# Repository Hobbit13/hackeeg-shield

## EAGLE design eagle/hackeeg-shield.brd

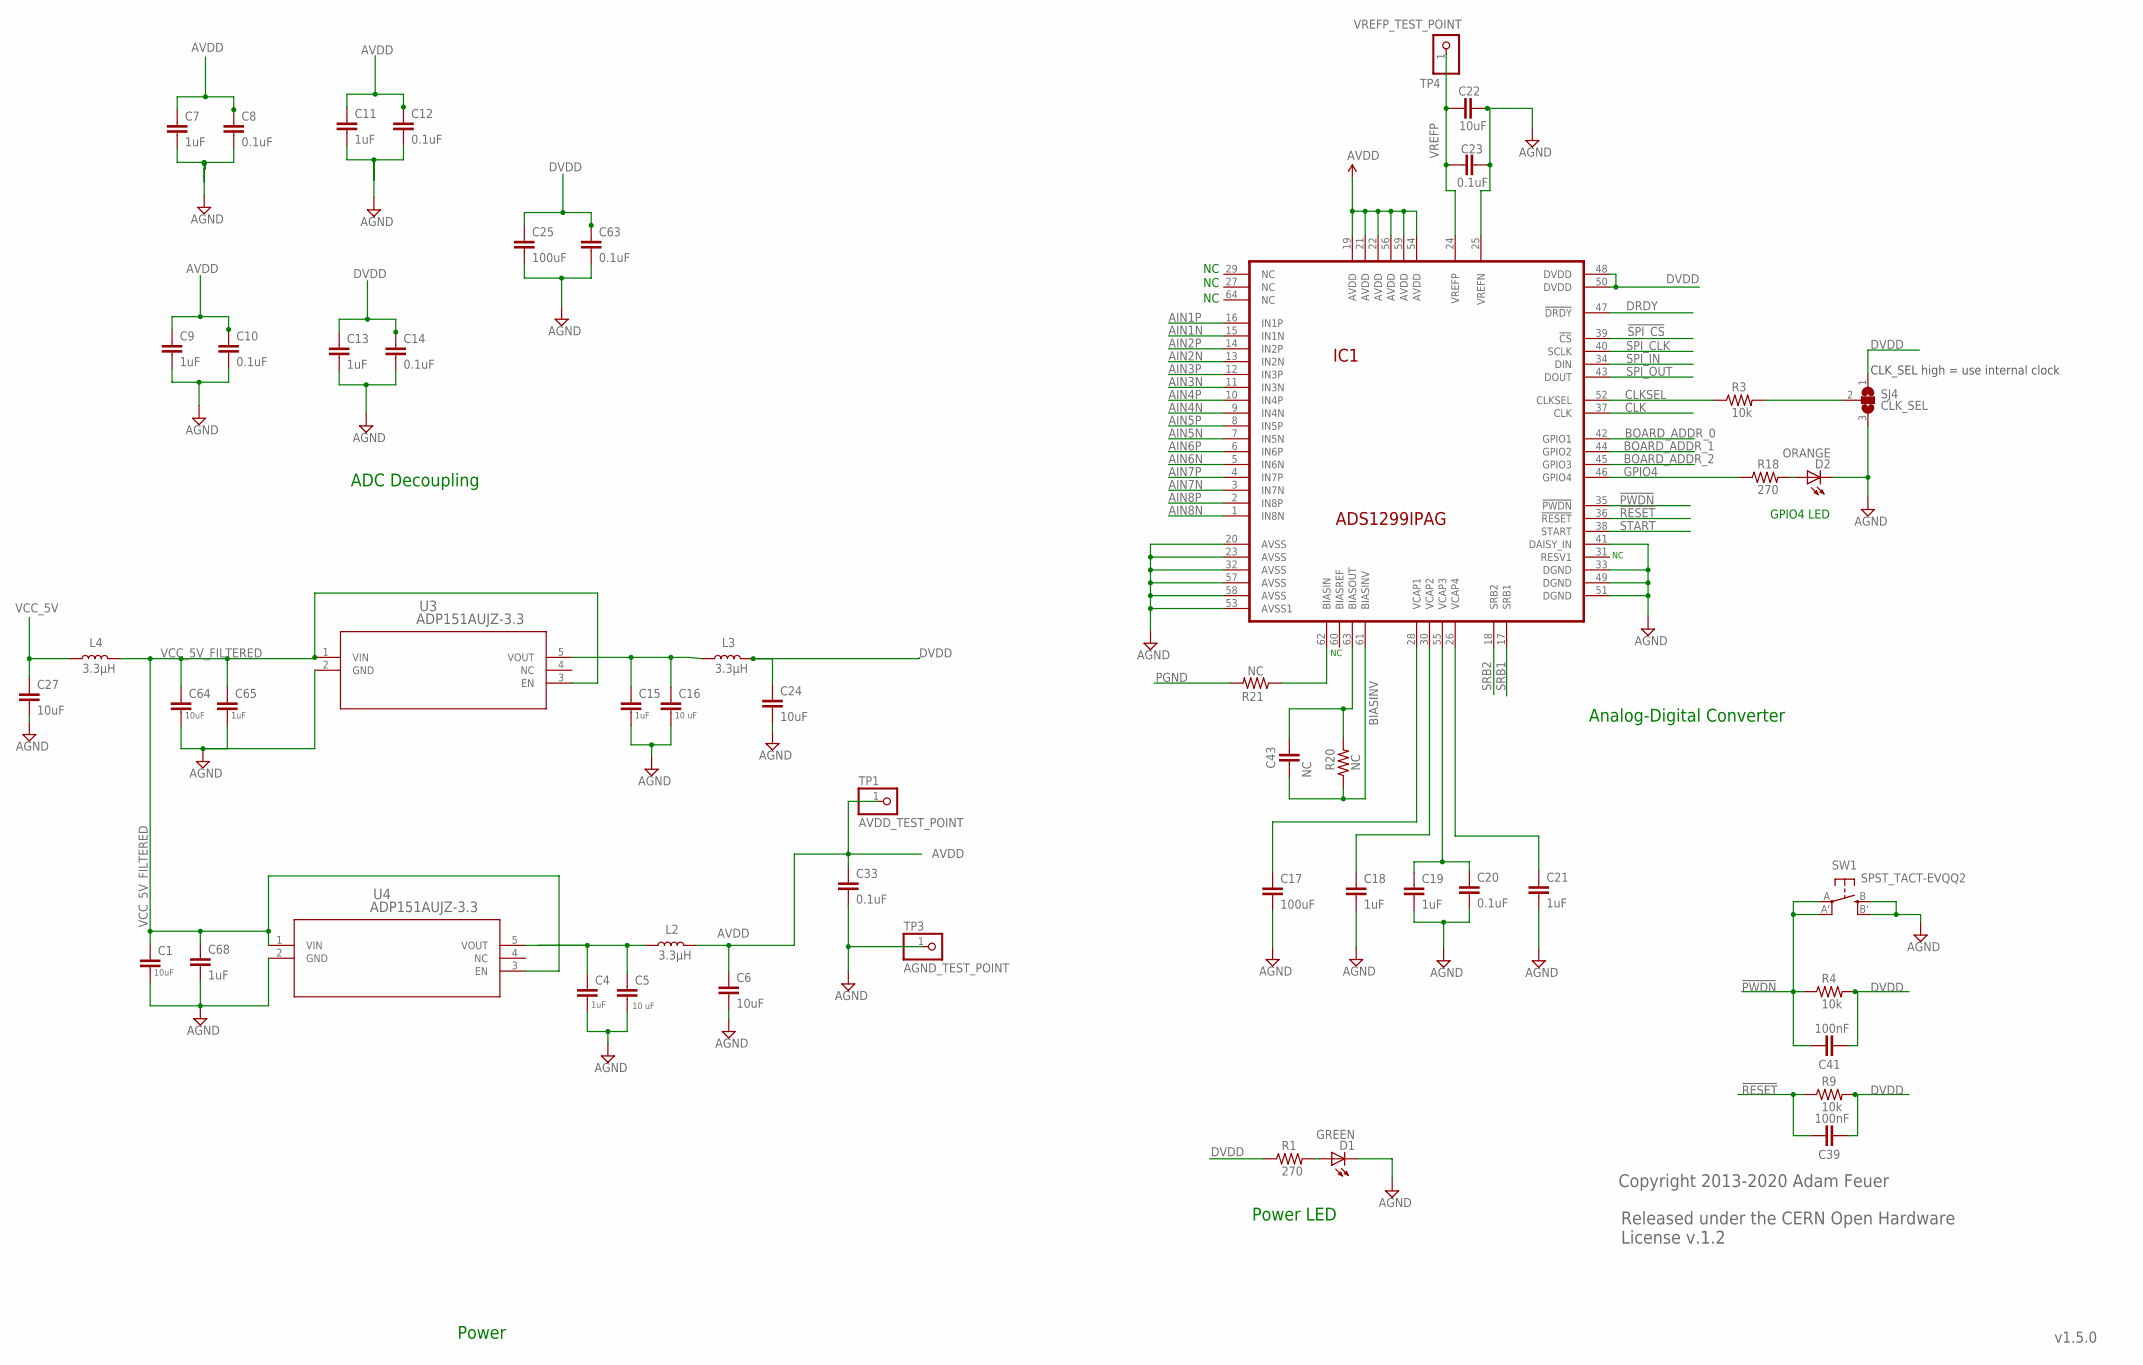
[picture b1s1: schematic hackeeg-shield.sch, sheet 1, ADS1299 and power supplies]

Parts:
C1, C6, C22, C24, C27, C64: 10uF; 0603-CAP
C4, C7, C9, C11, C13, C15, C18, C19, C21, C65, C68: 1uF; 0603-CAP
C5, C16: 10 uF; 0603-CAP
C8, C10, C12, C14, C20, C23, C33, C63: 0.1uF; 0603-CAP
C17, C25: 100uF; 1210
C39, C41: 100nF; 0603-CAP
C43: NC; 0603-CAP
D1: GREEN; LED-1206
D2: ORANGE; LED-1206
IC1: ADS1299IPAG; TQFP64
L2, L3, L4: 3.3μH; 0805-WIDE
R1, R18: 270; 0603-RES
R3, R4, R9: 10k; 0603-RES
R20, R21: NC; 0603-RES
SJ4: CLK_SEL; SJ_2
SW1: SPST_TACT-EVQQ2; EVQ-Q2
TP1: AVDD_TEST_POINT; 1X01
TP3: AGND_TEST_POINT; 1X01
TP4: VREFP_TEST_POINT; 1X01
U3, U4: ADP151AUJZ-3.3; UJ_5_ADI

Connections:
!PWDN: C41.1, IC1.35 (!PWDN), R4.1, SW1.A, SW1.A' (P1)
!RESET: C39.1, IC1.36 (!RESET), R9.1
!SPI_CS: IC1.39 (!CS); also elsewhere on the board
AGND: C1.2, C4.2, C5.2, C6.2, C7.2, C8.2, C9.2, C10.2, C11.2, C12.2, C13.2, C14.2, C15.2, C16.2, C17.2, C18.2, C19.2, C20.2, C21.2, C22.2, C23.2, C24.2, C25.2, C27.2, C33.2, C63.2, C64.2, C65.2, C68.2, D1.C, D2.C, IC1.20 (AVSS), IC1.23 (AVSS), IC1.25 (VREFN), IC1.32 (AVSS), IC1.33 (DGND), IC1.41 (DAISY_IN), IC1.49 (DGND), IC1.51 (DGND), IC1.53 (AVSS1), IC1.57 (AVSS), IC1.58 (AVSS), SJ4.3, SW1.B (S), SW1.B' (S1), TP3.1, U3.2 (GND), U4.2 (GND); also elsewhere on the board
AIN1N: IC1.15 (IN1N); also elsewhere on the board
AIN1P: IC1.16 (IN1P); also elsewhere on the board
AIN2N: IC1.13 (IN2N); also elsewhere on the board
AIN2P: IC1.14 (IN2P); also elsewhere on the board
AIN3N: IC1.11 (IN3N); also elsewhere on the board
AIN3P: IC1.12 (IN3P); also elsewhere on the board
AIN4N: IC1.9 (IN4N); also elsewhere on the board
AIN4P: IC1.10 (IN4P); also elsewhere on the board
AIN5N: IC1.7 (IN5N); also elsewhere on the board
AIN5P: IC1.8 (IN5P); also elsewhere on the board
AIN6N: IC1.5 (IN6N); also elsewhere on the board
AIN6P: IC1.6 (IN6P); also elsewhere on the board
AIN7N: IC1.3 (IN7N); also elsewhere on the board
AIN7P: IC1.4 (IN7P); also elsewhere on the board
AIN8N: IC1.1 (IN8N); also elsewhere on the board
AIN8P: IC1.2 (IN8P); also elsewhere on the board
AVDD: C6.1, C7.1, C8.1, C9.1, C10.1, C11.1, C12.1, C33.1, IC1.19 (AVDD), IC1.21 (AVDD), IC1.22 (AVDD), IC1.54 (AVDD), IC1.56 (AVDD), IC1.59 (AVDD), L2.2, TP1.1; also elsewhere on the board
BIASINV: C43.2, IC1.61 (BIASINV), R20.1; also elsewhere on the board
BOARD_ADDR_0: IC1.42 (GPIO1)
BOARD_ADDR_1: IC1.44 (GPIO2)
BOARD_ADDR_2: IC1.45 (GPIO3)
CLK: IC1.37 (CLK); also elsewhere on the board
CLKSEL: IC1.52 (CLKSEL), R3.1
DRDY: IC1.47 (!DRDY); also elsewhere on the board
DVDD: C13.1, C14.1, C24.1, C25.1, C39.2, C41.2, C63.1, IC1.48 (DVDD), IC1.50 (DVDD), L3.2, R1.1, R4.2, R9.2, SJ4.1; also elsewhere on the board
GPIO4: IC1.46 (GPIO4), R18.1
unnamed: C4.1, C5.1, L2.1, U4.5 (VOUT)
unnamed: C15.1, C16.1, L3.1, U3.5 (VOUT)
unnamed: C17.1, IC1.28 (VCAP1)
unnamed: C18.1, IC1.30 (VCAP2)
unnamed: C19.1, C20.1, IC1.55 (VCAP3)
unnamed: C21.1, IC1.26 (VCAP4)
unnamed: D2.A, R18.2
unnamed: D1.A, R1.2
unnamed: R3.2, SJ4.2
unnamed: C43.1, IC1.63 (BIASOUT), R20.2
unnamed: IC1.62 (BIASIN), R21.1
PGND: R21.2; also elsewhere on the board
SPI_CLK: IC1.40 (SCLK); also elsewhere on the board
SPI_IN: IC1.34 (DIN); also elsewhere on the board
SPI_OUT: IC1.43 (DOUT); also elsewhere on the board
SRB1: IC1.17 (SRB1); also elsewhere on the board
SRB2: IC1.18 (SRB2); also elsewhere on the board
START: IC1.38 (START); also elsewhere on the board
VCC_5V: C27.1, L4.1; also elsewhere on the board
VCC_5V_FILTERED: C1.1, C64.1, C65.1, C68.1, L4.2, U3.1 (VIN), U3.3 (EN), U4.1 (VIN), U4.3 (EN)
VREFP: C22.1, C23.1, IC1.24 (VREFP), TP4.1

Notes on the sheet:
Released under the CERN Open Hardware License v.1.2
Copyright 2013-2020 Adam Feuer
v1.5.0
ADC Decoupling
Power
Analog-Digital Converter
GPIO4 LED
Power LED
CLK_SEL high = use internal clock

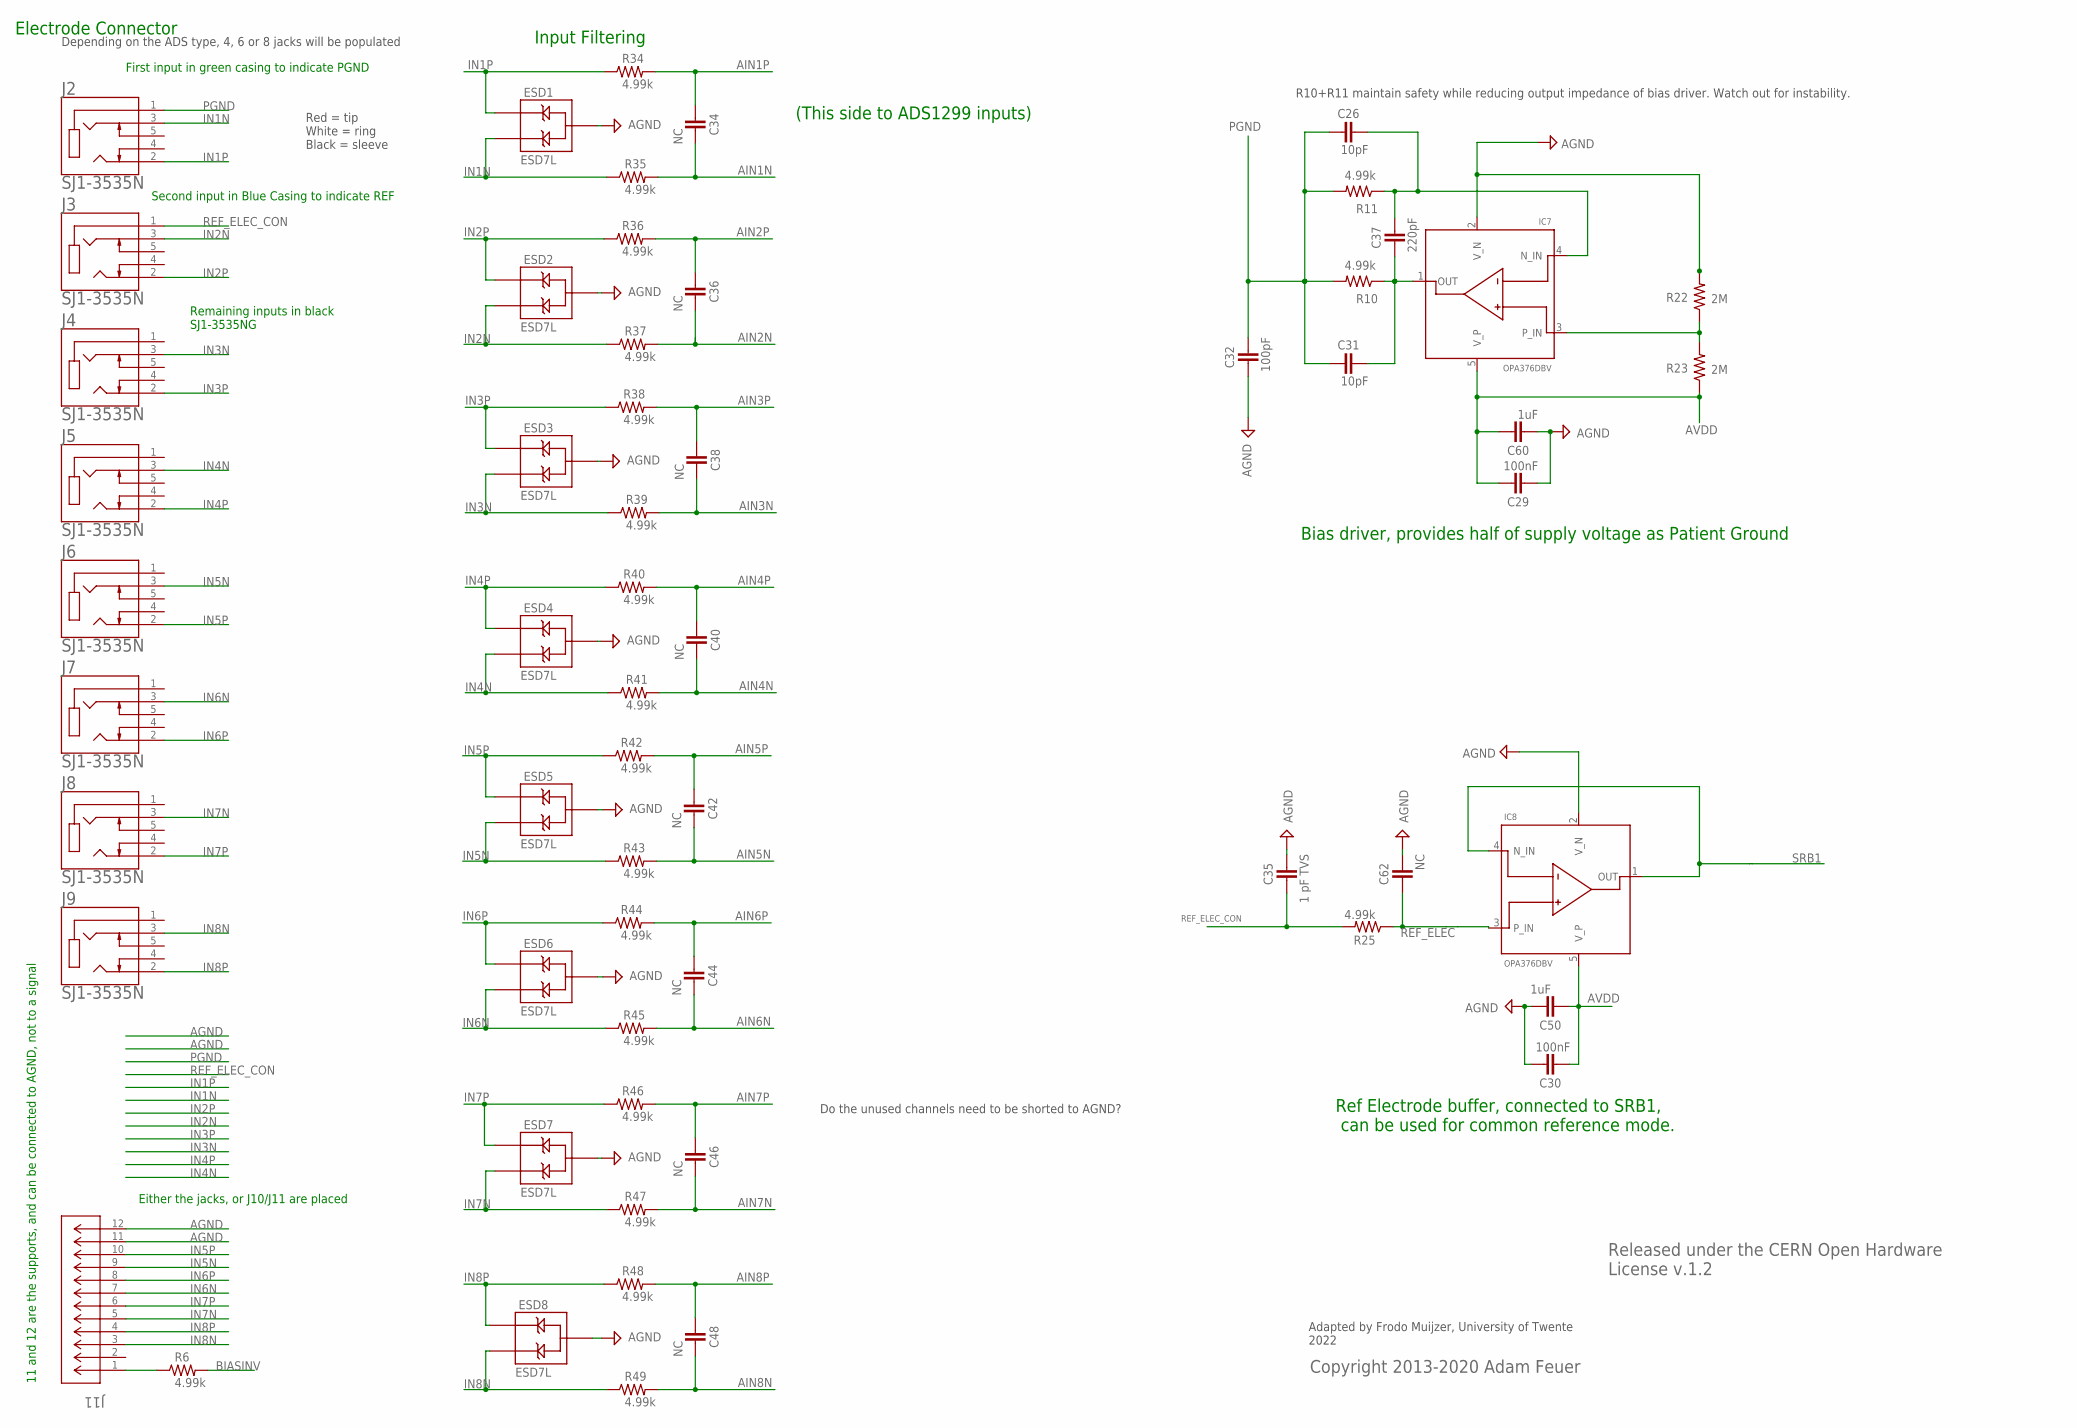
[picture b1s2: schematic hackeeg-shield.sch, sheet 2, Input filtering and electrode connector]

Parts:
C26, C31: 10pF; 0603-CAP
C29, C30: 100nF; 0603-CAP
C32: 100pF; 0603-CAP
C34, C36, C38, C40, C42, C44, C46, C48, C62: NC; 0603-CAP
C35: 1 pF TVS; 0603-CAP
C37: 220pF; 0603-CAP
C50, C60: 1uF; 0603-CAP
ESD1, ESD2, ESD3, ESD4, ESD5, ESD6, ESD7, ESD8: ESD7L; SOT-723
IC7, IC8: OPA376DBV; SOT23-5
J2, J3, J4, J5, J6, J7, J8, J9: SJ1-3535N; CUI_SJ1-3535N
J11: 533981071; CON_533981071
R6, R10, R11, R25, R34, R35, R36, R37, R38, R39, R40, R41, R42, R43, R44, R45, R46, R47, R48, R49: 4.99k; 0603-RES
R22, R23: 2M; 0603-RES

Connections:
AGND: C29.2, C30.1, C32.1, C35.2, C50.2, C60.2, C62.2, ESD1.P$3, ESD2.P$3, ESD3.P$3, ESD4.P$3, ESD5.P$3, ESD6.P$3, ESD7.P$3, ESD8.P$3, IC7.2 (V_N), IC8.2 (V_N), J11.11, J11.12, R22.2; also elsewhere on the board
AIN1N: C34.2, R35.2; also elsewhere on the board
AIN1P: C34.1, R34.2; also elsewhere on the board
AIN2N: C36.2, R37.2; also elsewhere on the board
AIN2P: C36.1, R36.2; also elsewhere on the board
AIN3N: C38.2, R39.2; also elsewhere on the board
AIN3P: C38.1, R38.2; also elsewhere on the board
AIN4N: C40.2, R41.2; also elsewhere on the board
AIN4P: C40.1, R40.2; also elsewhere on the board
AIN5N: C42.2, R43.2; also elsewhere on the board
AIN5P: C42.1, R42.2; also elsewhere on the board
AIN6N: C44.2, R45.2; also elsewhere on the board
AIN6P: C44.1, R44.2; also elsewhere on the board
AIN7N: C46.2, R47.2; also elsewhere on the board
AIN7P: C46.1, R46.2; also elsewhere on the board
AIN8N: C48.2, R49.2; also elsewhere on the board
AIN8P: C48.1, R48.2; also elsewhere on the board
AVDD: C29.1, C30.2, C50.1, C60.1, IC7.5 (V_P), IC8.5 (V_P), R23.1; also elsewhere on the board
BIASINV: R6.2; also elsewhere on the board
IN1N: ESD1.P$2, J2.3, R35.1
IN1P: ESD1.P$1, J2.2, R34.1
IN2N: ESD2.P$2, J3.3, R37.1
IN2P: ESD2.P$1, J3.2, R36.1
IN3N: ESD3.P$2, J4.3, R39.1
IN3P: ESD3.P$1, J4.2, R38.1
IN4N: ESD4.P$2, J5.3, R41.1
IN4P: ESD4.P$1, J5.2, R40.1
IN5N: ESD5.P$2, J6.3, J11.9, R43.1
IN5P: ESD5.P$1, J6.2, J11.10, R42.1
IN6N: ESD6.P$2, J7.3, J11.7, R45.1
IN6P: ESD6.P$1, J7.2, J11.8, R44.1
IN7N: ESD7.P$2, J8.3, J11.5, R47.1
IN7P: ESD7.P$1, J8.2, J11.6, R46.1
IN8N: ESD8.P$2, J9.3, J11.3, R49.1
IN8P: ESD8.P$1, J9.2, J11.4, R48.1
unnamed: J11.1, R6.1
unnamed: IC7.3 (P_IN), R22.1, R23.2
unnamed: C31.2, C37.1, IC7.1 (OUT), R10.1
unnamed: C26.2, C37.2, IC7.4 (N_IN), R11.1
PGND: C26.1, C31.1, C32.2, J2.1, R10.2, R11.2; also elsewhere on the board
REF_ELEC: C62.1, IC8.3 (P_IN), R25.1
REF_ELEC_CON: C35.1, J3.1, R25.2
SRB1: IC8.1 (OUT), IC8.4 (N_IN); also elsewhere on the board

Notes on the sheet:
Electrode Connector
Ref Electrode buffer, connected to SRB1, can be used for common reference mode.
Released under the CERN Open Hardware License v.1.2
Copyright 2013-2020 Adam Feuer
Input Filtering
(This side to ADS1299 inputs)
Red = tip White = ring Black = sleeve
R10+R11 maintain safety while reducing output impedance of bias driver. Watch out for instability.
Depending on the ADS type, 4, 6 or 8 jacks will be populated
Do the unused channels need to be shorted to AGND?
Adapted by Frodo Muijzer, University of Twente 2022
Bias driver, provides half of supply voltage as Patient Ground
First input in green casing to indicate PGND
Second input in Blue Casing to indicate REF
Remaining inputs in black SJ1-3535NG
11 and 12 are the supports, and can be connected to AGND, not to a signal
Either the jacks, or J10/J11 are placed

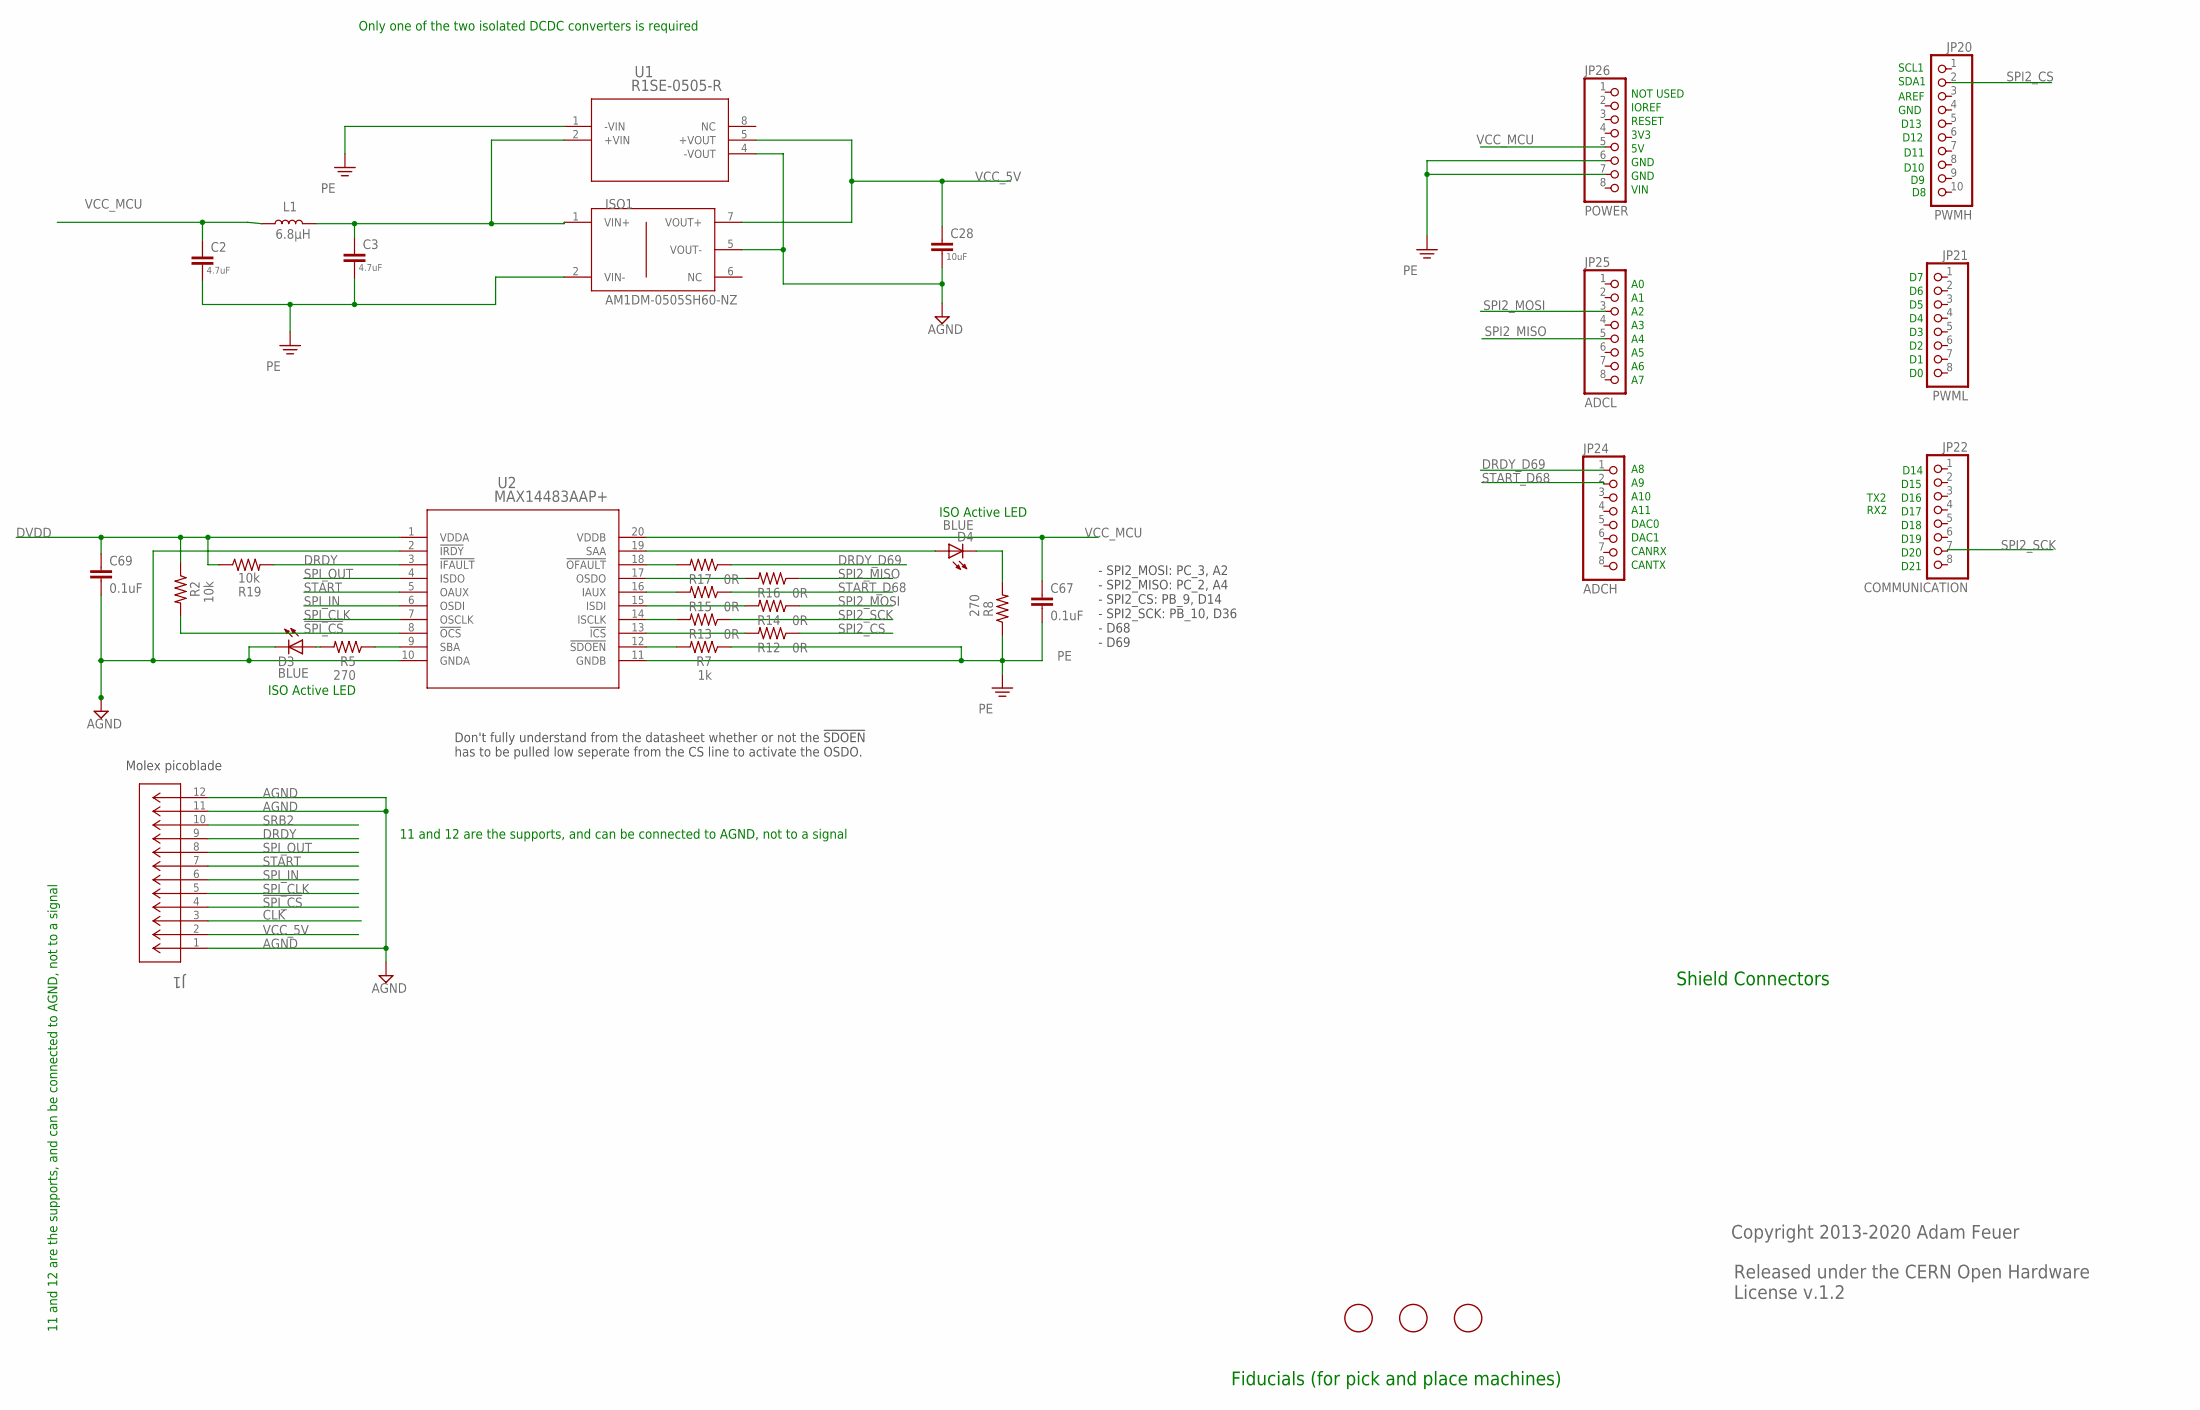
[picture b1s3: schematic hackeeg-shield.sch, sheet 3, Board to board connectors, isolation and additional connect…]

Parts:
C2, C3: 4.7uF; 0603-CAP
C28: 10uF; 0603-CAP
C67, C69: 0.1uF; 0603-CAP
D3, D4: BLUE; LED-1206
ISO1: AM1DM-0505SH60-NZ; SIP1005W50P254L1965H1265Q7
J1: 533981071; CON_533981071
JP20: PWMH; 1X10
JP21: PWML; 1X08
JP22: COMMUNICATION; 1X08
JP24: ADCH; 1X08
JP25: ADCL; 1X08
JP26: POWER; 1X08
L1: 6.8μH; 0805-WIDE
R2, R19: 10k; 0603-RES
R5, R8: 270; 0603-RES
R7: 1k; 0603-RES
R12, R13, R14, R15, R16, R17: 0R; 0603-RES
U1: R1SE-0505-R; R1SE-0505-R_RCP
U2: MAX14483AAP+; 21-0056C_20_MXM
U$2, U$5, U$6: FIDUCIAL; FIDUCIAL_1MM

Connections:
!SPI_CS: J1.4, R2.2, U2.8 (!OCS); also elsewhere on the board
AGND: C28.2, C69.2, D3.C, ISO1.5 (VOUT-), J1.1, J1.11, J1.12, U1.4 (-VOUT), U2.2 (!IRDY), U2.10 (GNDA); also elsewhere on the board
CLK: J1.3; also elsewhere on the board
DRDY: J1.9, R19.2, U2.3 (!IFAULT); also elsewhere on the board
DRDY_D69: JP24.1, R17.1
DVDD: C69.1, R2.1, R19.1, U2.1 (VDDA); also elsewhere on the board
unnamed: C3.1, ISO1.1 (VIN+), L1.2, U1.2 (+VIN)
unnamed: D4.A, U2.19 (SAA)
unnamed: D3.A, R5.2
unnamed: R5.1, U2.9 (SBA)
unnamed: R17.2, U2.18 (!OFAULT)
unnamed: D4.C, R8.2
unnamed: R12.2, U2.13 (!ICS)
unnamed: R13.2, U2.14 (ISCLK)
unnamed: R14.2, U2.15 (ISDI)
unnamed: R15.2, U2.16 (IAUX)
unnamed: R16.2, U2.17 (OSDO)
unnamed: R7.2, U2.12 (!SDOEN)
PE: C2.2, C3.2, C67.2, ISO1.2 (VIN-), JP26.6, JP26.7, R7.1, R8.1, U1.1 (-VIN), U2.11 (GNDB)
SPI2_CS: JP20.2, R12.1
SPI2_MISO: JP25.5, R16.1
SPI2_MOSI: JP25.3, R14.1
SPI2_SCK: JP22.7, R13.1
SPI_CLK: J1.5, U2.7 (OSCLK); also elsewhere on the board
SPI_IN: J1.6, U2.6 (OSDI); also elsewhere on the board
SPI_OUT: J1.8, U2.4 (ISDO); also elsewhere on the board
SRB2: J1.10; also elsewhere on the board
START: J1.7, U2.5 (OAUX); also elsewhere on the board
START_D68: JP24.2, R15.1
VCC_5V: C28.1, ISO1.7 (VOUT+), J1.2, U1.5 (+VOUT); also elsewhere on the board
VCC_MCU: C2.1, C67.1, JP26.5, L1.1, U2.20 (VDDB)

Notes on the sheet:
Released under the CERN Open Hardware License v.1.2
Copyright 2013-2020 Adam Feuer
Shield Connectors
SCL1
SDA1
AREF
GND
D14
D15
D16
D17
D18
D19
D20
D21
A10
A11
DAC0
DAC1
CANRX
CANTX
NOT USED
IOREF
RESET
3V3
VIN
Fiducials (for pick and place machines)
TX2
RX2
D13
D12
D11
D10
Only one of the two isolated DCDC converters is required
ISO Active LED
- SPI2_MOSI: PC_3, A2 - SPI2_MISO: PC_2, A4 - SPI2_CS: PB_9, D14 - SPI2_SCK: PB_10, D36 - D68 - D69
Don't fully understand from the datasheet whether or not the !SDOEN has to be pulled low seperate from the CS line to activate the OSDO.
Molex picoblade
11 and 12 are the supports, and can be connected to AGND, not to a signal

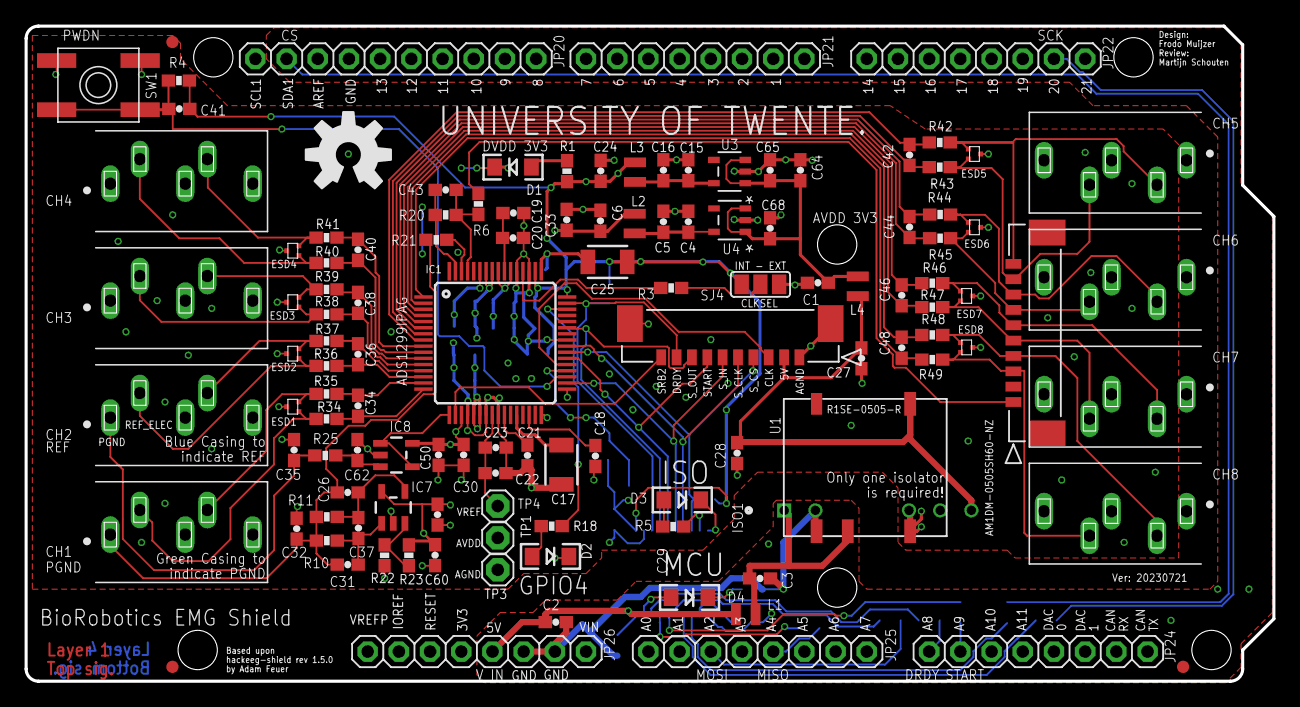
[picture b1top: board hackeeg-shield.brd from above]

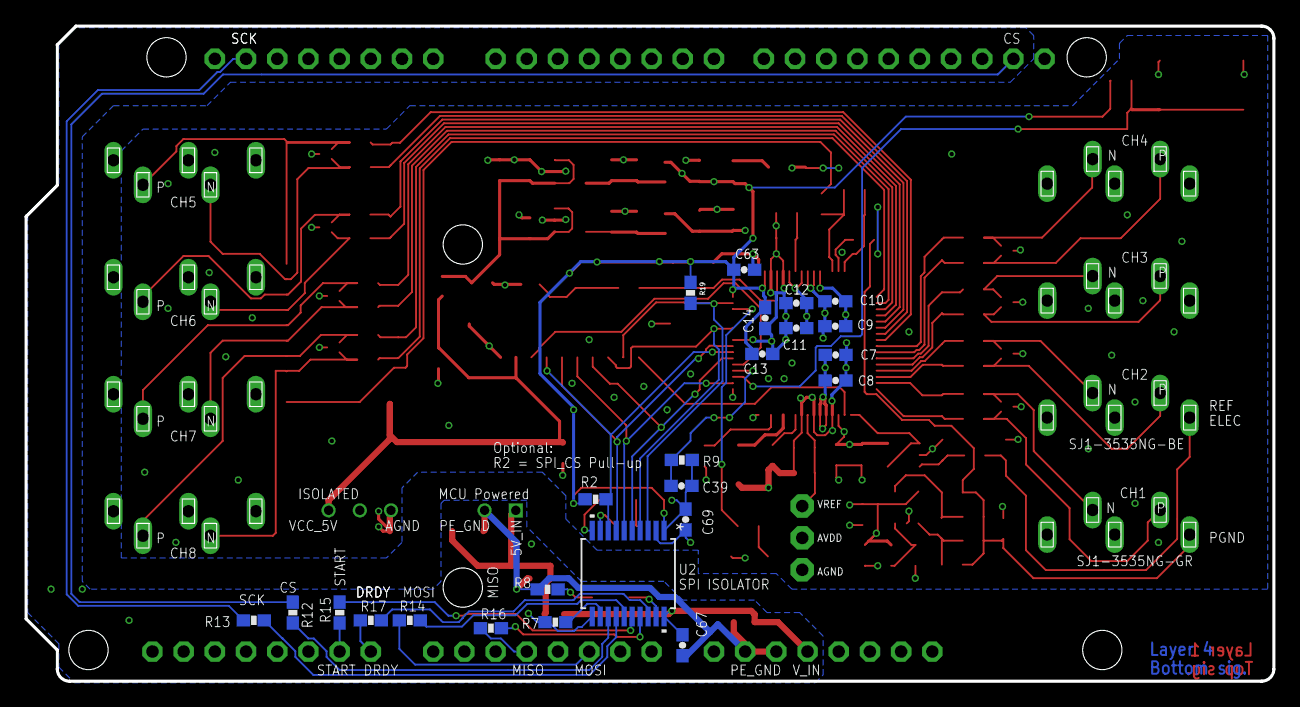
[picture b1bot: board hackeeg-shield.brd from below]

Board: 4 copper layers, 101.6 x 53.3 mm, 144 parts (24 on the bottom side), 90 nets.

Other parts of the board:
U$1: OSHW-LOGO-L

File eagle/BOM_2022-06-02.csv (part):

"Part";"Value";"Device";"Package";"Description";"AVAILABILITY";"COPYRIGHT";"CUI_PURCHASE_URL";"DESCRIPTION";"MANUFACTURER_PART_NUMBER";"MF";"MFR_NAME";"MP";"PACKAGE";"POPULARITY";"PRICE";"PROD_ID";"PURCHASE-URL";"VALUE";
"C1";"10uF";"CAP0603-CAP";"0603-CAP";"Capacitor";"";"";"";"";"";"";"";"";"";"";"";"";"";"";
"C2";"4.7uF";"CAP0603-CAP";"0603-CAP";"Capacitor";"";"";"";"";"";"";"";"";"";"";"";"";"";"";
"C3";"4.7uF";"CAP0603-CAP";"0603-CAP";"Capacitor";"";"";"";"";"";"";"";"";"";"";"";"";"";"";
"C4";"1uF";"CAP0603-CAP";"0603-CAP";"Capacitor";"";"";"";"";"";"";"";"";"";"";"";"";"";"";
"C5";"10 uF";"CAP0603-CAP";"0603-CAP";"Capacitor";"";"";"";"";"";"";"";"";"";"";"";"";"";"";
"C6";"10uF";"CAP0603-CAP";"0603-CAP";"Capacitor";"";"";"";"";"";"";"";"";"";"";"";"";"";"";
"C7";"1uF";"CAP0603-CAP";"0603-CAP";"Capacitor";"";"";"";"";"";"";"";"";"";"";"";"";"";"";
"C8";"0.1uF";"CAP0603-CAP";"0603-CAP";"Capacitor";"";"";"";"";"";"";"";"";"";"";"";"";"";"";
"C9";"1uF";"CAP0603-CAP";"0603-CAP";"Capacitor";"";"";"";"";"";"";"";"";"";"";"";"";"";"";
"C10";"0.1uF";"CAP0603-CAP";"0603-CAP";"Capacitor";"";"";"";"";"";"";"";"";"";"";"";"";"";"";
"C11";"1uF";"CAP0603-CAP";"0603-CAP";"Capacitor";"";"";"";"";"";"";"";"";"";"";"";"";"";"";
"C12";"0.1uF";"CAP0603-CAP";"0603-CAP";"Capacitor";"";"";"";"";"";"";"";"";"";"";"";"";"";"";
"C13";"1uF";"CAP0603-CAP";"0603-CAP";"Capacitor";"";"";"";"";"";"";"";"";"";"";"";"";"";"";
"C14";"0.1uF";"CAP0603-CAP";"0603-CAP";"Capacitor";"";"";"";"";"";"";"";"";"";"";"";"";"";"";
"C15";"1uF";"CAP0603-CAP";"0603-CAP";"Capacitor";"";"";"";"";"";"";"";"";"";"";"";"";"";"";
"C16";"10 uF";"CAP0603-CAP";"0603-CAP";"Capacitor";"";"";"";"";"";"";"";"";"";"";"";"";"";"";
"C17";"100uF";"CAP1210";"1210";"Capacitor";"";"";"";"";"";"";"";"";"";"";"";"";"";"";
"C18";"1uF";"CAP0603-CAP";"0603-CAP";"Capacitor";"";"";"";"";"";"";"";"";"";"";"";"";"";"";
"C19";"1uF";"CAP0603-CAP";"0603-CAP";"Capacitor";"";"";"";"";"";"";"";"";"";"";"";"";"";"";
"C20";"0.1uF";"CAP0603-CAP";"0603-CAP";"Capacitor";"";"";"";"";"";"";"";"";"";"";"";"";"";"";
"C21";"1uF";"CAP0603-CAP";"0603-CAP";"Capacitor";"";"";"";"";"";"";"";"";"";"";"";"";"";"";
"C22";"10uF";"CAP0603-CAP";"0603-CAP";"Capacitor";"";"";"";"";"";"";"";"";"";"";"";"";"";"";
"C23";"0.1uF";"CAP0603-CAP";"0603-CAP";"Capacitor";"";"";"";"";"";"";"";"";"";"";"";"";"";"";
"C24";"10uF";"CAP0603-CAP";"0603-CAP";"Capacitor";"";"";"";"";"";"";"";"";"";"";"";"";"";"";
"C25";"100uF";"CAP1210";"1210";"Capacitor";"";"";"";"";"";"";"";"";"";"";"";"";"";"";
"C26";"10pF";"CAP0603-CAP";"0603-CAP";"Capacitor";"";"";"";"";"";"";"";"";"";"";"";"";"";"";
"C27";"10uF";"CAP0603-CAP";"0603-CAP";"Capacitor";"";"";"";"";"";"";"";"";"";"";"";"";"";"";
"C28";"10uF";"CAP0603-CAP";"0603-CAP";"Capacitor";"";"";"";"";"";"";"";"";"";"";"";"";"";"";
"C29";"100nF";"CAP0603-CAP";"0603-CAP";"Capacitor";"";"";"";"";"";"";"";"";"";"";"";"";"";"";
"C30";"100nF";"CAP0603-CAP";"0603-CAP";"Capacitor";"";"";"";"";"";"";"";"";"";"";"";"";"";"";
"C31";"10pF";"CAP0603-CAP";"0603-CAP";"Capacitor";"";"";"";"";"";"";"";"";"";"";"";"";"";"";
"C32";"100pF";"CAP0603-CAP";"0603-CAP";"Capacitor";"";"";"";"";"";"";"";"";"";"";"";"";"";"";
"C33";"0.1uF";"CAP0603-CAP";"0603-CAP";"Capacitor";"";"";"";"";"";"";"";"";"";"";"";"";"";"";
"C34";"NC";"CAP0603-CAP";"0603-CAP";"Capacitor";"";"";"";"";"";"";"";"";"";"";"";"";"";"";
"C35";"1 pF TVS";"CAP0603-CAP";"0603-CAP";"Capacitor";"";"";"";"";"";"";"";"";"";"";"";"";"";"";
"C36";"NC";"CAP0603-CAP";"0603-CAP";"Capacitor";"";"";"";"";"";"";"";"";"";"";"";"";"";"";
"C37";"220pF";"CAP0603-CAP";"0603-CAP";"Capacitor";"";"";"";"";"";"";"";"";"";"";"";"";"";"";
"C38";"NC";"CAP0603-CAP";"0603-CAP";"Capacitor";"";"";"";"";"";"";"";"";"";"";"";"";"";"";
"C39";"100nF";"CAP0603-CAP";"0603-CAP";"Capacitor";"";"";"";"";"";"";"";"";"";"";"";"";"";"";
"C40";"NC";"CAP0603-CAP";"0603-CAP";"Capacitor";"";"";"";"";"";"";"";"";"";"";"";"";"";"";
"C41";"100nF";"CAP0603-CAP";"0603-CAP";"Capacitor";"";"";"";"";"";"";"";"";"";"";"";"";"";"";
"C42";"NC";"CAP0603-CAP";"0603-CAP";"Capacitor";"";"";"";"";"";"";"";"";"";"";"";"";"";"";
"C44";"NC";"CAP0603-CAP";"0603-CAP";"Capacitor";"";"";"";"";"";"";"";"";"";"";"";"";"";"";
"C46";"NC";"CAP0603-CAP";"0603-CAP";"Capacitor";"";"";"";"";"";"";"";"";"";"";"";"";"";"";
"C48";"NC";"CAP0603-CAP";"0603-CAP";"Capacitor";"";"";"";"";"";"";"";"";"";"";"";"";"";"";
"C50";"1uF";"CAP0603-CAP";"0603-CAP";"Capacitor";"";"";"";"";"";"";"";"";"";"";"";"";"";"";
"C60";"1uF";"CAP0603-CAP";"0603-CAP";"Capacitor";"";"";"";"";"";"";"";"";"";"";"";"";"";"";
"C62";"NC";"CAP0603-CAP";"0603-CAP";"Capacitor";"";"";"";"";"";"";"";"";"";"";"";"";"";"";
"C63";"0.1uF";"CAP0603-CAP";"0603-CAP";"Capacitor";"";"";"";"";"";"";"";"";"";"";"";"";"";"";
"C64";"10uF";"CAP0603-CAP";"0603-CAP";"Capacitor";"";"";"";"";"";"";"";"";"";"";"";"";"";"";
"C65";"1uF";"CAP0603-CAP";"0603-CAP";"Capacitor";"";"";"";"";"";"";"";"";"";"";"";"";"";"";
"C67";"0.1uF";"CAP0603-CAP";"0603-CAP";"Capacitor";"";"";"";"";"";"";"";"";"";"";"";"";"";"";
"C68";"1uF";"CAP0603-CAP";"0603-CAP";"Capacitor";"";"";"";"";"";"";"";"";"";"";"";"";"";"";
"C69";"0.1uF";"CAP0603-CAP";"0603-CAP";"Capacitor";"";"";"";"";"";"";"";"";"";"";"";"";"";"";
"D1";"RED";"LED-RED1206";"LED-1206";"Assorted Red LEDs";"";"";"";"";"";"";"";"";"";"";"";"DIO-00809";"";"RED";
"D2";"BLUE";"LED-WHITE";"LED-1206";"White SMD LEDs";"";"";"";"";"";"";"";"";"";"";"";"DIO-09955";"";"WHITE";
"D3";"BLUE";"LED-WHITE";"LED-1206";"White SMD LEDs";"";"";"";"";"";"";"";"";"";"";"";"DIO-09955";"";"WHITE";
"D4";"BLUE";"LED-WHITE";"LED-1206";"White SMD LEDs";"";"";"";"";"";"";"";"";"";"";"";"DIO-09955";"";"WHITE";
"ESD1";"ESD7L";"ESD7L";"SOT-723";"PolMar  Check availability";"In Stock";"";"";" 10.4V Clamp 1A (8/20µs) Ipp Tvs Diode Surface Mount SOT-723 ";"";"ON Semiconductor";"";"ESD7L";"SOT-723 ON Semiconductor";"";"None";"";"https://pricing.snapeda.com/search/part/ESD7L/?ref=eda";"";
"ESD2";"ESD7L";"ESD7L";"SOT-723";"PolMar  Check availability";"In Stock";"";"";" 10.4V Clamp 1A (8/20µs) Ipp Tvs Diode Surface Mount SOT-723 ";"";"ON Semiconductor";"";"ESD7L";"SOT-723 ON Semiconductor";"";"None";"";"https://pricing.snapeda.com/search/part/ESD7L/?ref=eda";"";
"ESD3";"ESD7L";"ESD7L";"SOT-723";"PolMar  Check availability";"In Stock";"";"";" 10.4V Clamp 1A (8/20µs) Ipp Tvs Diode Surface Mount SOT-723 ";"";"ON Semiconductor";"";"ESD7L";"SOT-723 ON Semiconductor";"";"None";"";"https://pricing.snapeda.com/search/part/ESD7L/?ref=eda";"";
"ESD4";"ESD7L";"ESD7L";"SOT-723";"PolMar  Check availability";"In Stock";"";"";" 10.4V Clamp 1A (8/20µs) Ipp Tvs Diode Surface Mount SOT-723 ";"";"ON Semiconductor";"";"ESD7L";"SOT-723 ON Semiconductor";"";"None";"";"https://pricing.snapeda.com/search/part/ESD7L/?ref=eda";"";
"ESD5";"ESD7L";"ESD7L";"SOT-723";"PolMar  Check availability";"In Stock";"";"";" 10.4V Clamp 1A (8/20µs) Ipp Tvs Diode Surface Mount SOT-723 ";"";"ON Semiconductor";"";"ESD7L";"SOT-723 ON Semiconductor";"";"None";"";"https://pricing.snapeda.com/search/part/ESD7L/?ref=eda";"";
"ESD6";"ESD7L";"ESD7L";"SOT-723";"PolMar  Check availability";"In Stock";"";"";" 10.4V Clamp 1A (8/20µs) Ipp Tvs Diode Surface Mount SOT-723 ";"";"ON Semiconductor";"";"ESD7L";"SOT-723 ON Semiconductor";"";"None";"";"https://pricing.snapeda.com/search/part/ESD7L/?ref=eda";"";
"ESD7";"ESD7L";"ESD7L";"SOT-723";"PolMar  Check availability";"In Stock";"";"";" 10.4V Clamp 1A (8/20µs) Ipp Tvs Diode Surface Mount SOT-723 ";"";"ON Semiconductor";"";"ESD7L";"SOT-723 ON Semiconductor";"";"None";"";"https://pricing.snapeda.com/search/part/ESD7L/?ref=eda";"";
"ESD8";"ESD7L";"ESD7L";"SOT-723";"PolMar  Check availability";"In Stock";"";"";" 10.4V Clamp 1A (8/20µs) Ipp Tvs Diode Surface Mount SOT-723 ";"";"ON Semiconductor";"";"ESD7L";"SOT-723 ON Semiconductor";"";"None";"";"https://pricing.snapeda.com/search/part/ESD7L/?ref=eda";"";
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
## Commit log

2022-07-28 Modified version that uses isolated SPI and isolated DC-DC converter (not tested much!)
    To enable use of the EMG shield while the Arduino is galvanically connected to mains (in our scenario since it also containers motor driver controllers).
    Basic communication works, but signal quality is not tested yet.
    Issues:
    - Spikes in signals, probably SPI issues
    - MCU led polarity is wrong
    - AIMTEC isolator doesn't fit well (keep out area is on the wrong side)
2023-04-21 Patched led, removed header ch1 to 4, added drdy pull up
2023-07-25 added NC res/cap to potentially use the RLD
    Added C and R between 61 and 63 and moved R6 closer to chip, to enable testing with RLD and future patch to enable it.

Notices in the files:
eagle/BOM_2022-06-02.csv:
"533981071";"533981071";"CON_533981071";"";"";"Copyright (C) 2022 Ultra Librarian. All rights reserved.";"";"";"533981071";"";"Molex Connector Corporation";"";"";"";"";"";"";"";
"R1SE-0505-R";"R1SE-0505-R";"R1SE-0505-R_RCP";"";"";"Copyright (C) 2022 Ultra Librarian. All rights reserved.";"";"";"R1SE-0505-R";"";"Recom Power";"";"";"";"";"";"";"";
"MAX14483AAP+";"MAX14483AAP+";"21-0056C_20_MXM";"";"";"Copyright (C) 2022 Ultra Librarian. All rights reserved.";"";"";"MAX14483AAP+";"";"Maxim Integrated Products";"";"";"";"";"";"";"";
